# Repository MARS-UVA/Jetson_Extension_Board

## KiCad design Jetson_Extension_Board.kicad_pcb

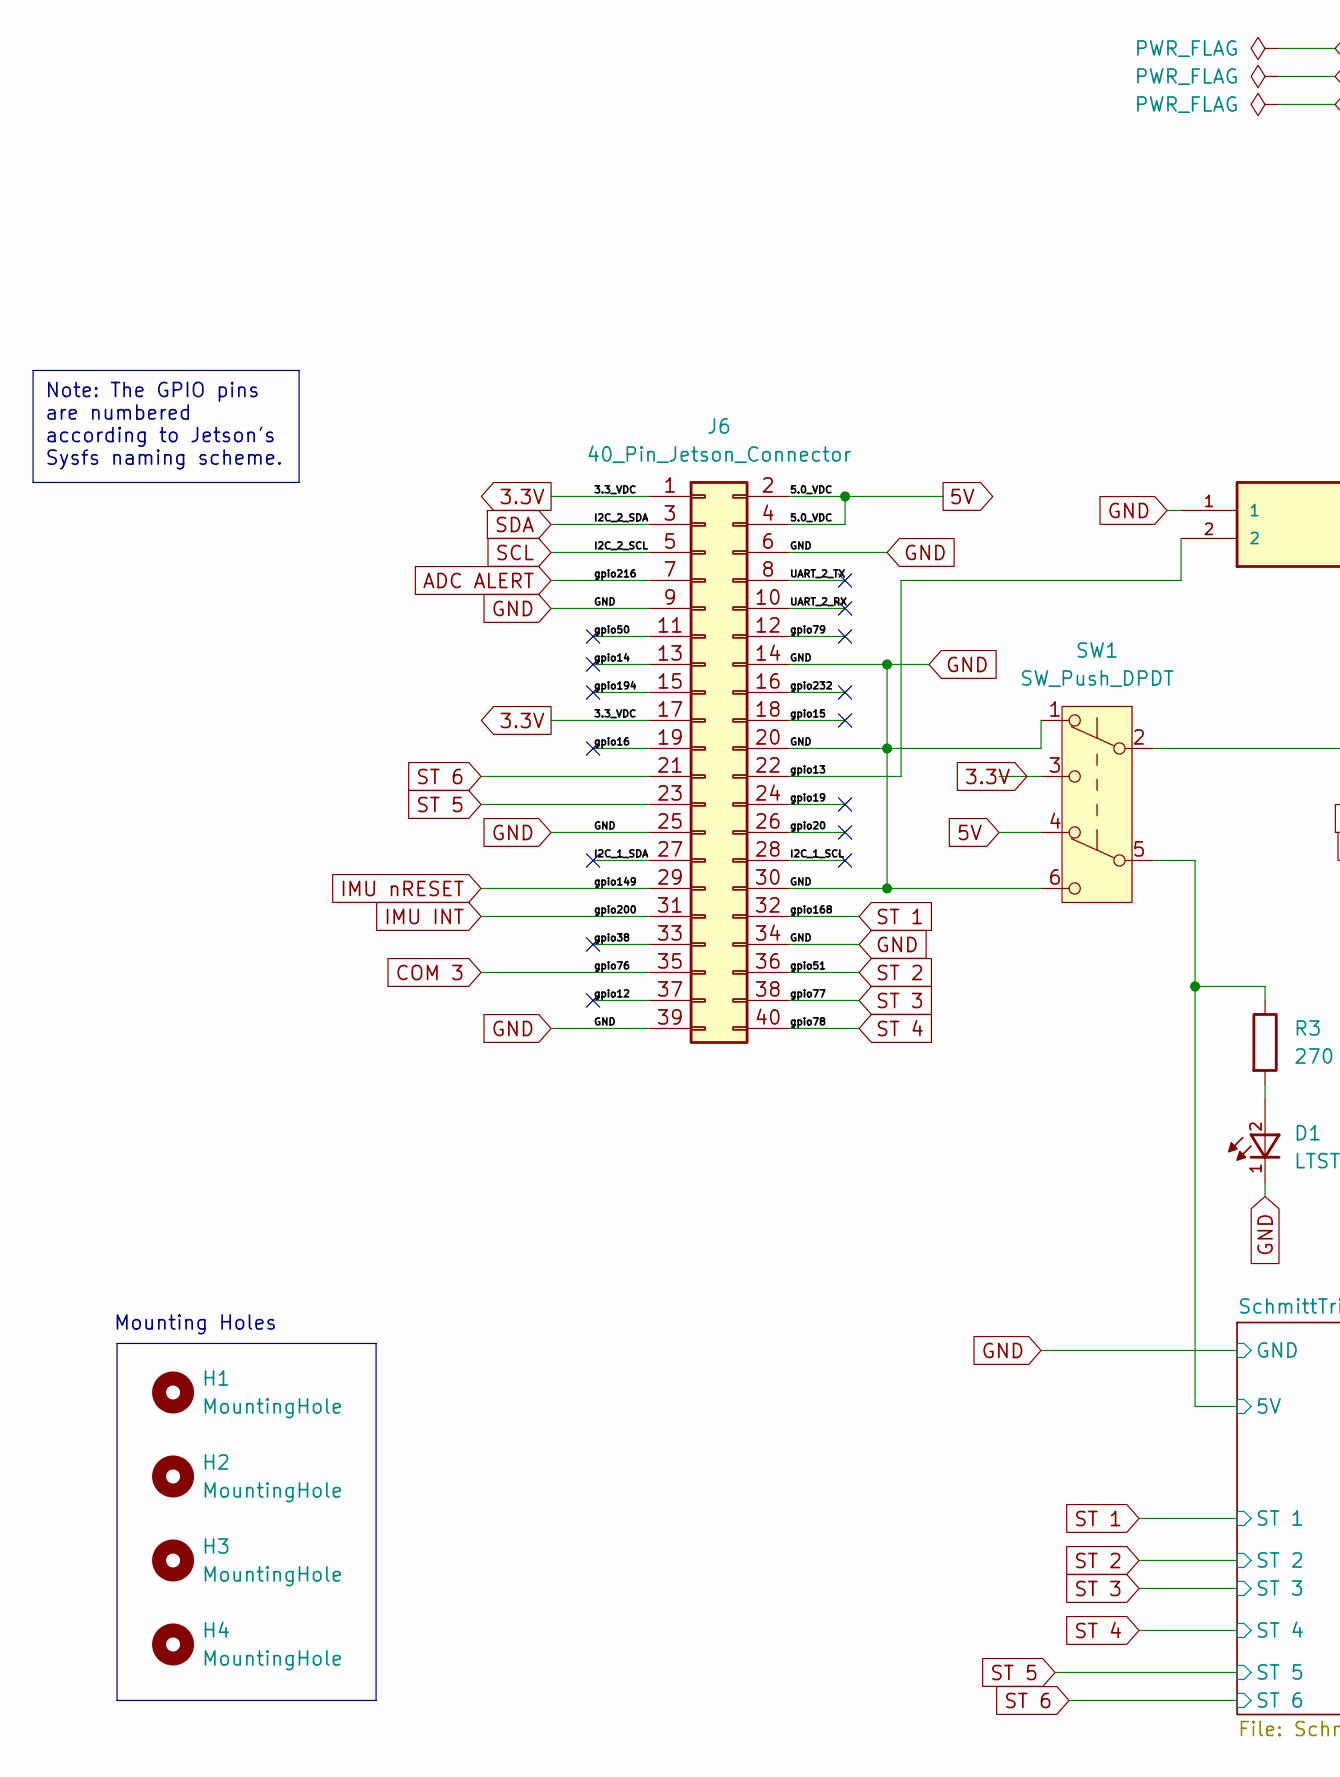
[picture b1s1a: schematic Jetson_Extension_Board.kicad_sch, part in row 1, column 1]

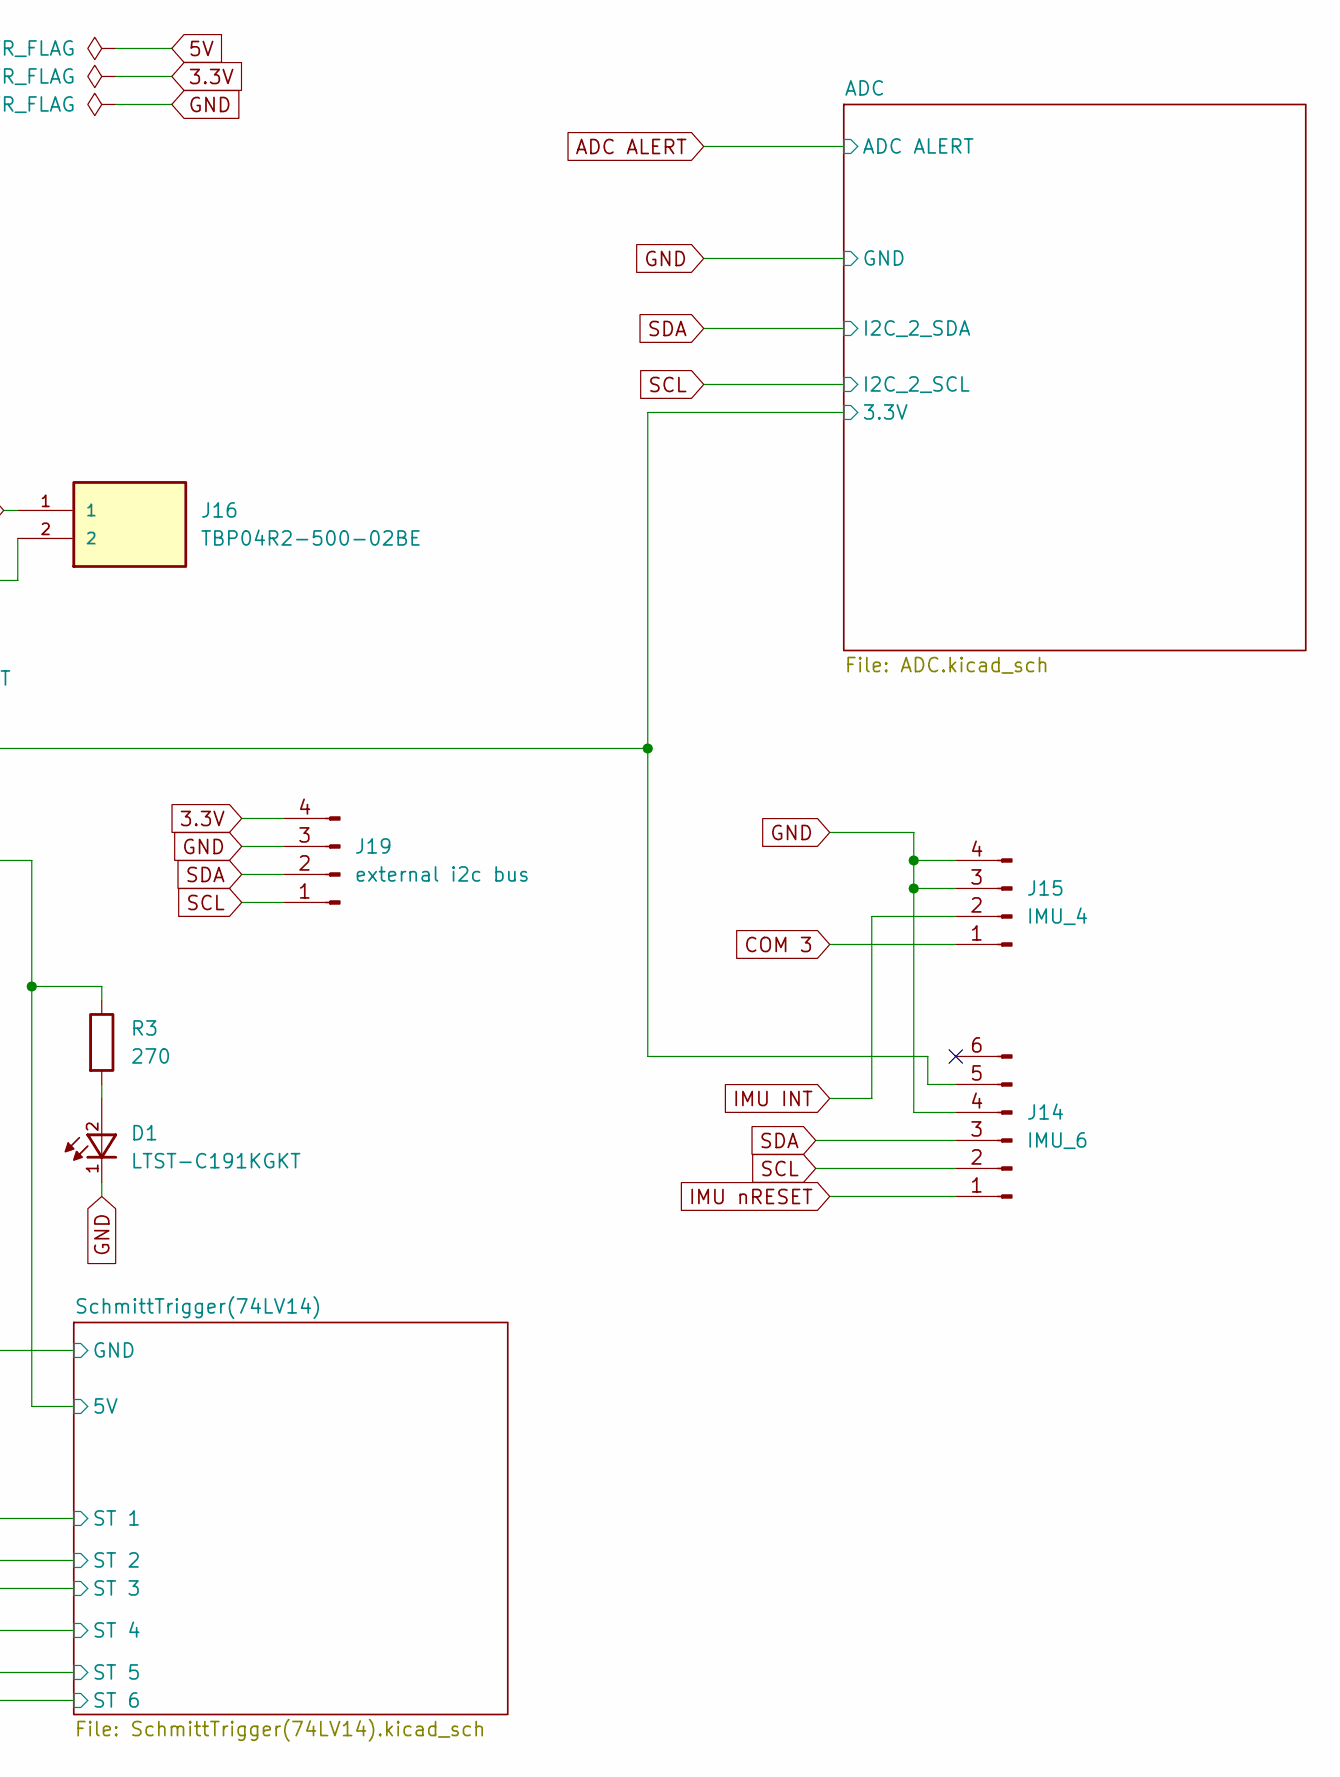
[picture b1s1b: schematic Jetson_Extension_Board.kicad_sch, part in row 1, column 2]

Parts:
D1: LTST-C191KGKT; 0603
H1, H2, H3, H4: MountingHole; MountingHole_2.1mm
J6: 40_Pin_Jetson_Connector; PinHeader_2x20_P2.54mm_Vertical
J14: IMU_6; PinSocket_1x06_P2.54mm_Vertical
J15: IMU_4; PinSocket_1x04_P2.54mm_Vertical
J16: TBP04R2-500-02BE; CUI_TBP04R2-500-02BE; PARTREV 1.0
J19: external i2c bus; TBP04R2-500-04BE
R3: 270; R_1206_3216Metric
SW1: SW_Push_DPDT; SW_CK_JS202011AQN_DPDT_Angled

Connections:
3.3V: J6.1, J6.17, J19.4, SW1.3 (C)
5V: J6.2, J6.4, SW1.4 (A)
/ADC/3.3V: J14.5, SW1.2 (B); also elsewhere on the board
/I2C_1_SCL: J6.28
/I2C_1_SDA: J6.27
/SchmittTrigger(74LV14)/5V: R3.1, SW1.5 (B); also elsewhere on the board
/UART_2_RX: J6.10
/UART_2_TX: J6.8
/gpio12: J6.37
/gpio13: J6.22, J16.2; also elsewhere on the board
/gpio14: J6.13
/gpio15: J6.18
/gpio16: J6.19
/gpio19: J6.24
/gpio20: J6.26
/gpio38: J6.33
/gpio50: J6.11
/gpio79: J6.12
/gpio194: J6.15
/gpio232: J6.16
ADC ALERT: J6.7; also elsewhere on the board
COM 3: J6.35, J15.1
GND: D1.1, J6.6, J6.9, J6.14, J6.20, J6.25, J6.30, J6.34, J6.39, J14.4, J15.3, J15.4, J16.1, J19.3, SW1.1 (A), SW1.6 (C); also elsewhere on the board
IMU INT: J6.31, J15.2
IMU nRESET: J6.29, J14.1
unnamed: D1.2, R3.2
SCL: J6.5, J14.2, J19.1; also elsewhere on the board
SDA: J6.3, J14.3, J19.2; also elsewhere on the board
ST 1: J6.32; also elsewhere on the board
ST 2: J6.36; also elsewhere on the board
ST 3: J6.38; also elsewhere on the board
ST 4: J6.40; also elsewhere on the board
ST 5: J6.23; also elsewhere on the board
ST 6: J6.21; also elsewhere on the board

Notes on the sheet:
Note: The GPIO pins are numbered according to Jetson's Sysfs naming scheme.
Mounting Holes

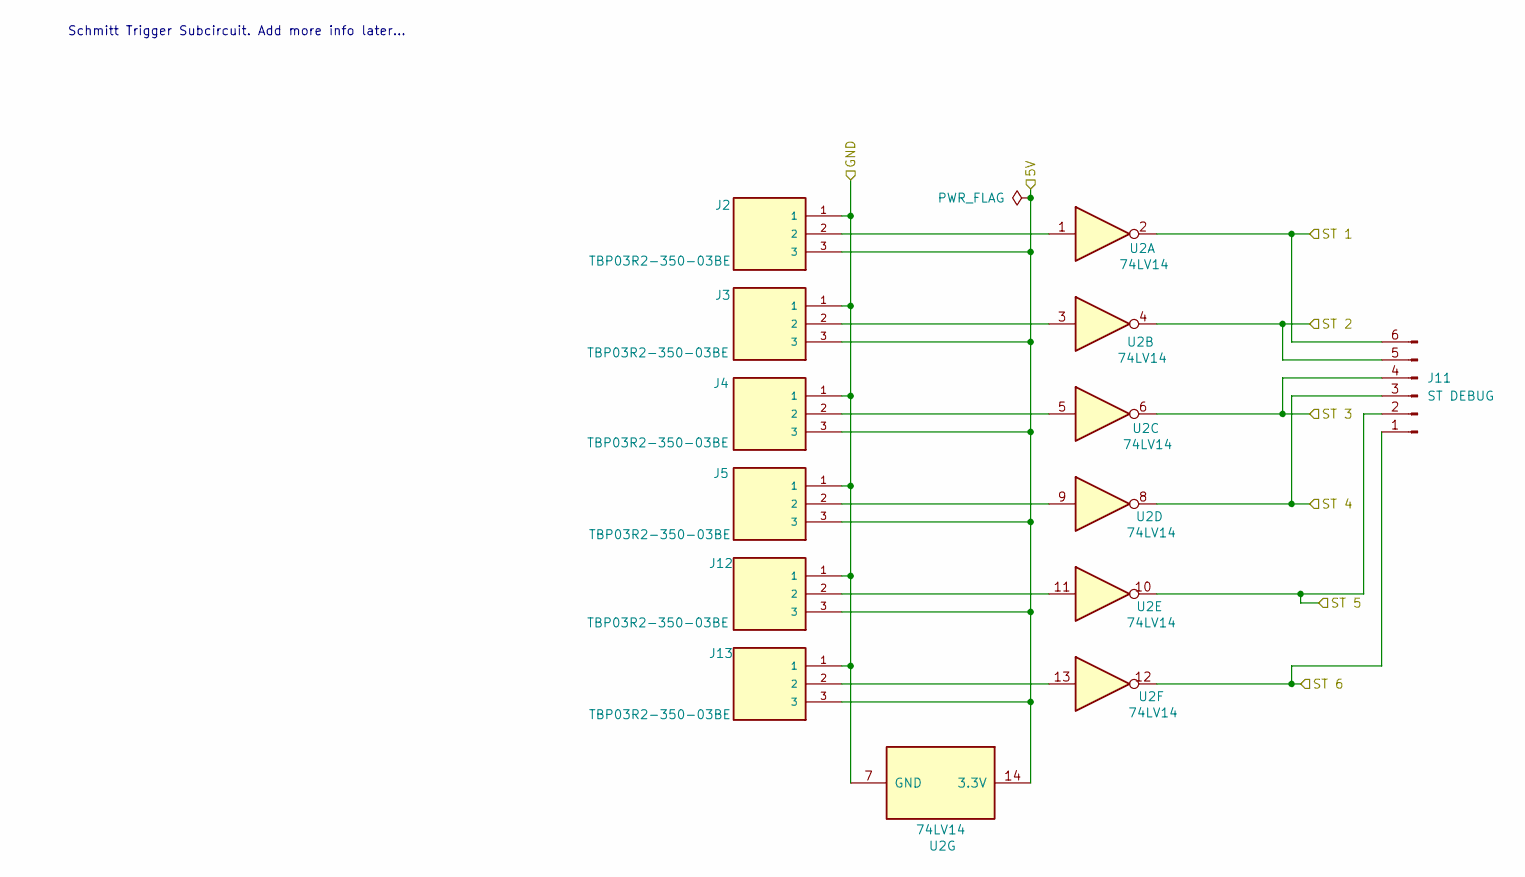
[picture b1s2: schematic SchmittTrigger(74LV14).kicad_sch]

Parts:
J2, J3, J4, J5, J12, J13: TBP03R2-350-03BE; CUI_TBP03R2-350-03BE; PARTREV 1.0
J11: ST DEBUG; PinSocket_1x06_P2.54mm_Vertical
U2: 74LV14; DIP-14_W7.62mm_Socket

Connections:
/SchmittTrigger(74LV14)/5V: J2.3, J3.3, J4.3, J5.3, J12.3, J13.3, U2.14 (3.3V); also elsewhere on the board
GND: J2.1, J3.1, J4.1, J5.1, J12.1, J13.1, U2.7 (GND); also elsewhere on the board
unnamed: J2.2, U2.1
unnamed: J3.2, U2.3
unnamed: J4.2, U2.5
unnamed: J5.2, U2.9
unnamed: J12.2, U2.11
unnamed: J13.2, U2.13
ST 1: J11.6, U2.2; also elsewhere on the board
ST 2: J11.5, U2.4; also elsewhere on the board
ST 3: J11.4, U2.6; also elsewhere on the board
ST 4: J11.3, U2.8; also elsewhere on the board
ST 5: J11.2, U2.10; also elsewhere on the board
ST 6: J11.1, U2.12; also elsewhere on the board

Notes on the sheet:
Schmitt Trigger Subcircuit. Add more info later...

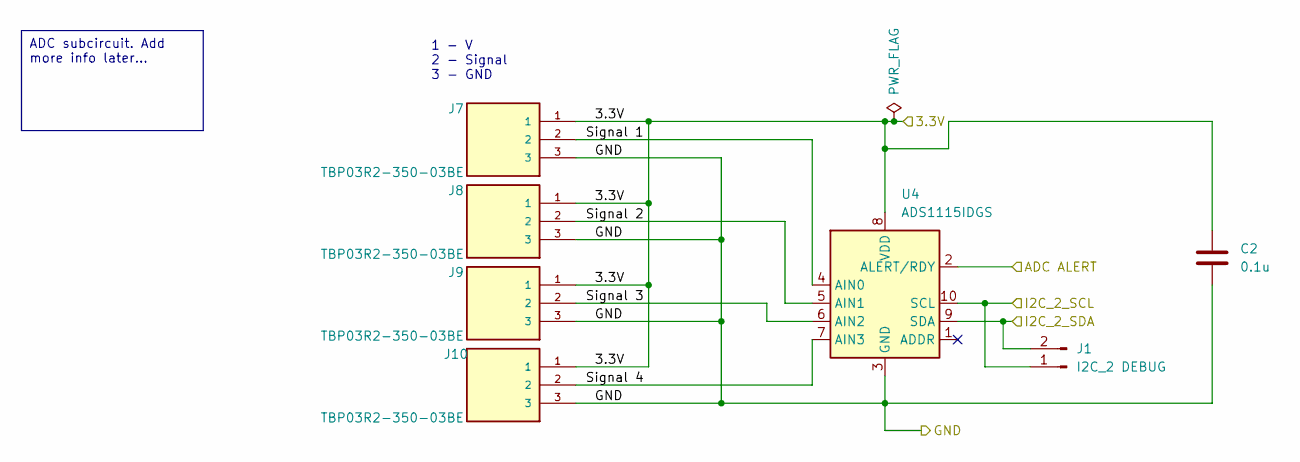
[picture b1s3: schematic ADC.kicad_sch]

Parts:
C2: 0.1u; C_1206_3216Metric
J1: I2C_2 DEBUG; PinSocket_1x02_P2.54mm_Vertical
J7, J8, J9, J10: TBP03R2-350-03BE; CUI_TBP03R2-350-03BE; PARTREV 1.0
U4: ADS1115IDGS; TSSOP-10_3x3mm_P0.5mm

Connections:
/ADC/3.3V: C2.1, J7.1, J8.1, J9.1, J10.1, U4.8 (VDD); also elsewhere on the board
/ADC/Signal 1: J7.2, U4.4 (AIN0)
/ADC/Signal 2: J8.2, U4.5 (AIN1)
/ADC/Signal 3: J9.2, U4.6 (AIN2)
/ADC/Signal 4: J10.2, U4.7 (AIN3)
ADC ALERT: U4.2 (ALERT/RDY); also elsewhere on the board
GND: C2.2, J7.3, J8.3, J9.3, J10.3, U4.3 (GND); also elsewhere on the board
SCL: J1.1, U4.10 (SCL); also elsewhere on the board
SDA: J1.2, U4.9 (SDA); also elsewhere on the board

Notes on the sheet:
ADC subcircuit. Add more info later...
1 - V 2 - Signal 3 - GND

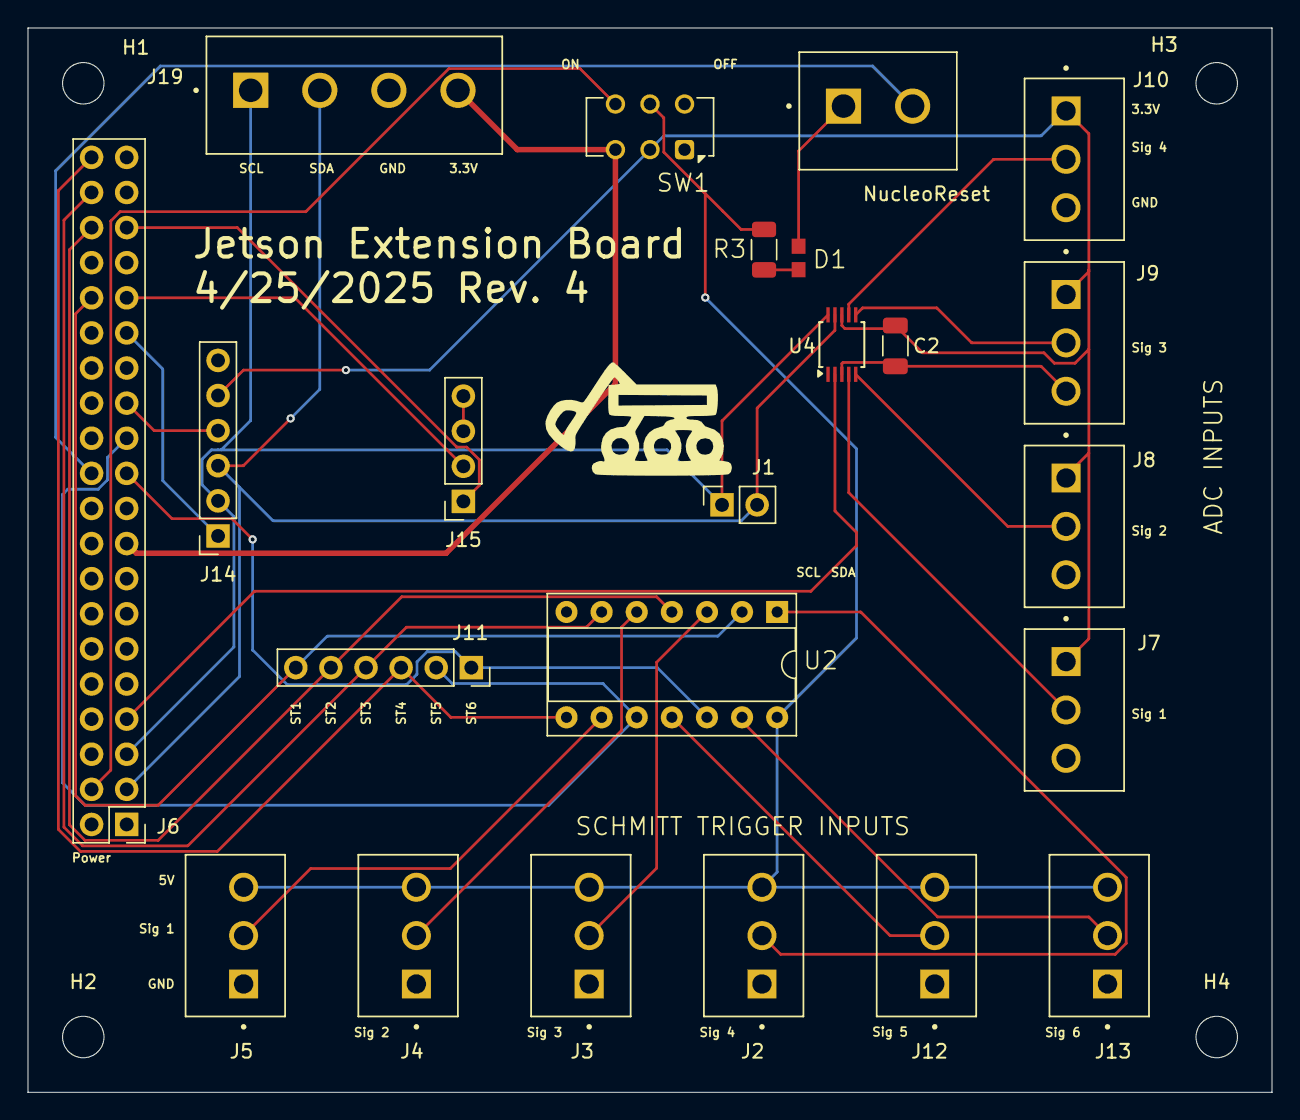
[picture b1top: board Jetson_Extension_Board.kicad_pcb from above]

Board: 2 copper layers, 90.0 x 77.0 mm, 27 parts (0 on the bottom side), 29 nets.

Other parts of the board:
NucleoReset: TBP04R2-500-02BE; CUI_TBP04R2-500-02BE

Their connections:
/gpio13: NucleoReset.2; also elsewhere on the board
GND: NucleoReset.1; also elsewhere on the board

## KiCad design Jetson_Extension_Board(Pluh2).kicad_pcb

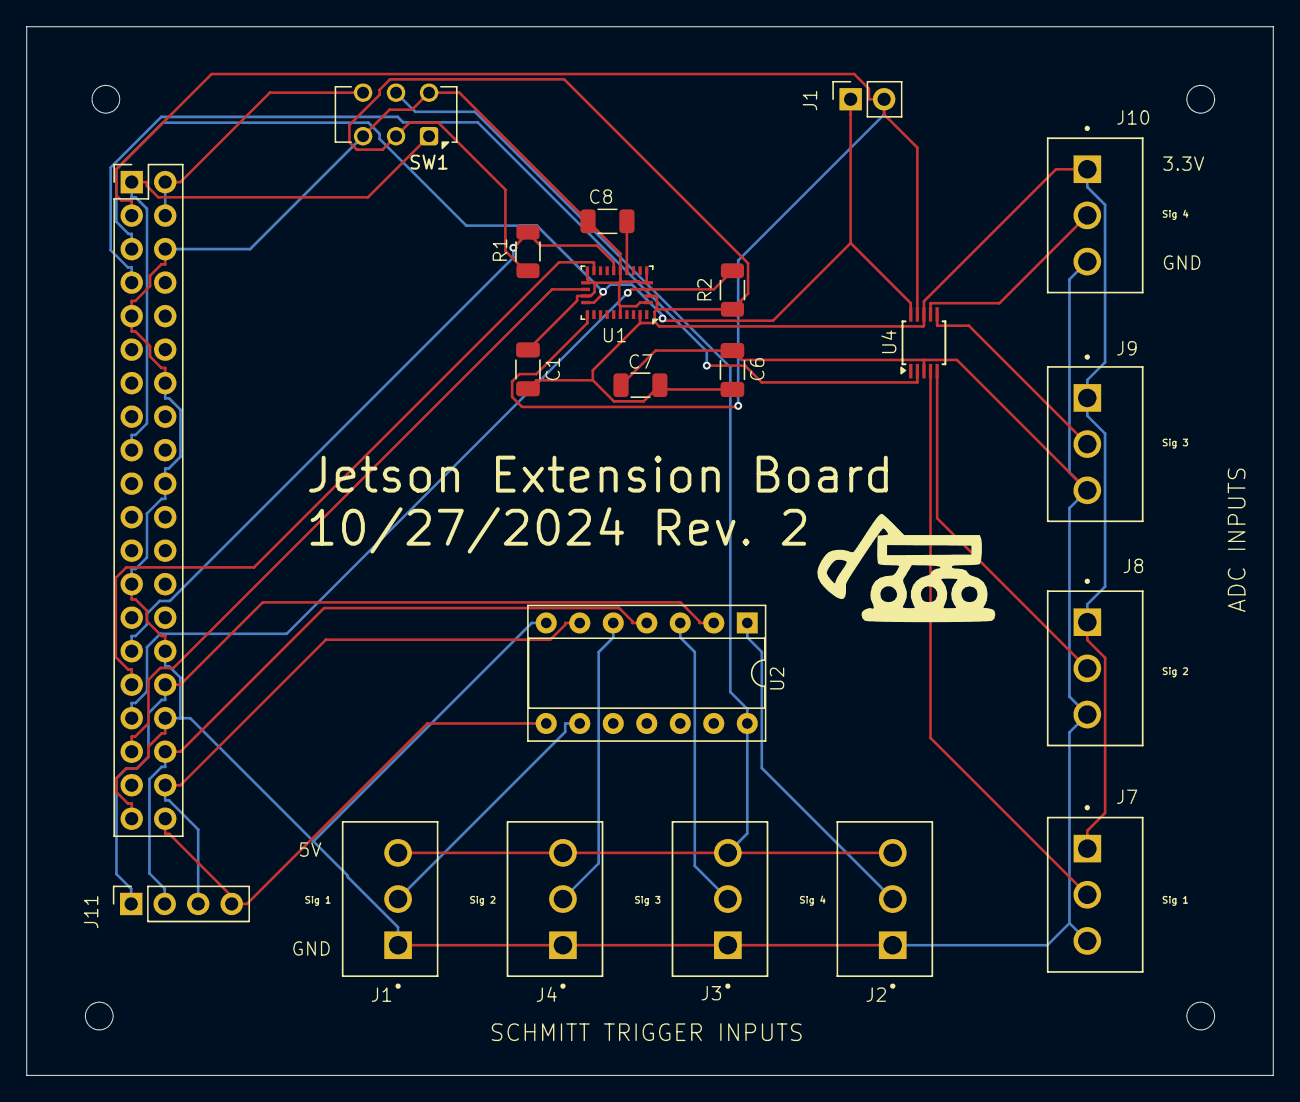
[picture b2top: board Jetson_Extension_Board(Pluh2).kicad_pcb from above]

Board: 2 copper layers, 94.5 x 79.5 mm, 25 parts (1 on the bottom side), 25 nets.

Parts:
C1: 120n; C_1206_3216Metric
C6, C8: 100n; C_1206_3216Metric
C7: 6.8n; C_1206_3216Metric
H1, H2, H3, H4: MountingHole; MountingHole_2.1mm
J1: I2C_2 DEBUG; PinSocket_1x02_P2.54mm_Vertical
J2, J3, J4, J5, J7, J8, J9, J10: TBP03R2-350-03BE; CUI_TBP03R2-350-03BE
J6: 40_Pin_Jetson_Connector; PinHeader_2x20_P2.54mm_Vertical
J11: ST DEBUG; PinSocket_1x04_P2.54mm_Vertical
R1, R2: 10k; R_1206_3216Metric
SW1: SW_Push_DPDT; SW_CK_JS202011AQN_DPDT_Angled
U1: BNO055; LGA-28_5.2x3.8mm_P0.5mm
U2: 74LV14; DIP-14_W7.62mm_Socket
U4: ADS1115IDGS; TSSOP-10_3x3mm_P0.5mm

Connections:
3.3V: J6.1, J6.17, SW1.1 (A)
5V: J6.2, J6.4, SW1.4 (A)
/ADC/3.3V: C1.2, C6.2, C7.2, J7.1, J8.1, J9.1, J10.1, R1.1, R2.1, SW1.2 (B), U1.3 (VDD), U1.28 (VDDIO), U4.8 (VDD)
/ADC/Signal 1: J7.2, U4.4 (AIN0)
/ADC/Signal 2: J8.2, U4.5 (AIN1)
/ADC/Signal 3: J9.2, U4.6 (AIN2)
/ADC/Signal 4: J10.2, U4.7 (AIN3)
/I2C_2_SCL: J1.1, J6.5, U1.19 (COM1), U4.10 (SCL)
/I2C_2_SDA: J1.2, J6.3, U1.20 (COM0), U4.9 (SDA)
/SchmittTrigger(74LV14)/5V: J2.3, J3.3, J4.3, J5.3, SW1.5 (B), U2.14 (5V)
ADC ALERT: J6.7, U4.2 (ALERT/RDY)
COM 3: J6.35, U1.17 (COM3)
GND: C1.1, C6.1, C7.1, C8.2, J2.1, J3.1, J4.1, J5.1, J6.6, J6.9, J6.14, J6.20, J6.25, J6.30, J6.34, J6.39, J7.3, J8.3, J9.3, J10.3, SW1.3 (C), SW1.6 (C), U1.2 (GND), U1.5 (PS1), U1.6 (PS0), U1.10 (BL_IND), U1.15 (GNDIO), U1.16 (GNDIO), U1.18 (COM2), U1.25 (GNDIO), U2.7 (GND), U4.3 (GND)
IMU INT: J6.31, U1.14 (INT)
IMU nBOOT: J6.33, R2.2, U1.4 (~BOOT_LOAD_PIN)
IMU nRESET: J6.29, R1.2, U1.11 (~RESET)
unnamed: J2.2, U2.1
unnamed: J3.2, U2.3
unnamed: J4.2, U2.5
unnamed: J5.2, U2.9
unnamed: C8.1, U1.9 (CAP)
ST 1: J6.32, J11.1, U2.2
ST 2: J6.36, J11.2, U2.4
ST 3: J6.38, J11.3, U2.6
ST 4: J6.40, J11.4, U2.8

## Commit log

2024-10-06 Version 2 of ADS1115 Subcircuit
    Change power voltage to 3.3V and added 100 nF decoupling capacitor
2024-10-06 Schmitt Trigger Subcircuit
2024-10-06 ADS1115 Subcircuit V3
    Added footprint for the capacitor & changed voltage values on terminal inputs to 3.3V
2024-10-08 Whole Circuit Integration
2024-10-09 Replaced sockets with terminal blocks
2024-10-11 Reorganized schematic and resolved ERC errors
    Resolved some of the ERC errors related to disconnected pins and power flags. Renamed GPIO pins on 40-pin header. Changed ADC power supply to 3.3V and schmitt trigger circuit power supply to 5V. Conn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
    Also moved IMU and 40-pin header KiCAD project files into their own folders.
2024-10-11 Renamed the project file to Jetson_Extension_Board
2024-10-11 Imported Footprints
2024-10-11 Attempted to implement constraints
2024-10-11 Started PCB Layout
2024-10-11 Added Layout file
2024-10-11 PCB Layout attempted 1
2024-10-18 Worked on PCB Layout
2024-10-20 Deleted some extra files
    Deleted Jetson_Extension_Board2.5 and Jetson_Extension_Board2.5.1 Files
2024-10-20 Add debug pins and switch
2024-10-20 Revert "Add debug pins and switch"
2024-10-20 Finished PCB Layout
2024-10-20 Created Gerber and Drill FIles
2024-10-22 Fixed Errors
2024-10-22 debug pins schematic done and pcb partial
2024-10-25 Worked on PCB
2024-10-27 Fixed Some Constraints
2024-10-27 Fixed All Constraints
2024-10-27 Freerouted attempt
2024-10-27 More stuff yuh
2024-10-27 (Pluh 2) is the current second revision
2024-10-27 Pluh 1 and 2 removed, main file is updated version
2024-10-27 LEDS
    consolidated file, added diode and resistor (look over), and silkscreen errors present
2024-10-27 Added Correct LED
2024-10-27 Created New Gerber and Drill Files
2024-10-30 Edited silkscreen
    Added labels for debug pins
2024-11-02 Changed the resistor value of R3
    R3 is 270 ohms instead of 260 ohms.
2025-01-09 deleted extraneous files
2025-01-26 PCB Update
2025-01-29 added connectors for pots and compacted further
2025-01-31 changed hole sizes, added labels, added ground plane, set trace width min
2025-02-02 alignment fixes
2025-02-02 added i2c bus pins, fixed errors, is ready for a final review
2025-02-05 made more fixes to JEB
2025-02-07 replaced pot blocks with a nucleo reset block
2025-02-07 fixed hole sizes
2025-02-07 actually fixed holes this time
2025-02-07 labels moved
2025-02-25 Modified constraints and routing
    Set constraints according to JLCPCB specifications.
2025-02-28 Generated Gerbers
    Also made slight modifications to routing and added board info to back silkscreen
2025-02-28 Generated front paste layer
    Added front paste layer to gerber files
2025-03-01 added front paste layer to gerber zip file
2025-04-25 v4 pcb
    drc: didn't connect 3.3v pins and 5v pins and some gnd pins are not connected to gnd plane; they are connected within the jetson, and I don't think it's necessary to connect them on the jeb. all comp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
